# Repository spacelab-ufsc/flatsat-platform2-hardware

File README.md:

<h1 align="center">
	FLATSAT PLATFORM V2.0 - HARDWARE
	<br>
</h1>

<h4 align="center">Hardware project of the FlatSat Platform 2.0, designed and developed by SpaceLab.</h4>

<p align="center">

</p>

<details>
    <summary>Summary</summary>
    <ol>
        <li>
            <a href="#overview">Overview</a>
        </li>
        <li>
            <a href="#repository-organization">Repository Organization</a>
        </li>
        <li>
            <a href="#license">License</a>
        </li>
        <li>
            <a href="#releases">Releases</a>
        </li>
        <li>
            <a href="#notes">Notes</a>
        </li>
        <li>
            <a href="#references">References</a>
        </li>
    </ol>
</details>

## Overview
The **FlatSat Platform 2.0** is a testbench for testing the main SpaceLab's subsystems, but can be adapted for other CubeSat missions. A FlatSat is an electrical model of the satellite with the subsystems assembled side by side over a workbench that can be mounted during the V&V [[1]](#1). They offer an easier, faster and safer way for testing subsystems before assembly into the final structure of a CubeSat. It can be used in combination with the hardware-in-the-loop (HIL) technique, which justifies the usage of a built-in MicroZed and sensors. Moreover, it supports up to 6 modules. This platform is intended to function as an electrical ground support equipment (EGSE) for the SpaceLab team, leveraging the MicroZed, sensors, and future daughterboards to emulate and simulate diverse mission scenarios. Additionally, it facilitates comprehensive system-level and subsystem-level testing. The FlatSat Platform itself is presented in [[2]](#2).

This repository contains the hardware project of the FlatSat Platform 2.0 (schematics, PCB layout, libraries and fabrication files), developed in KiCad.

<p align="center">

</p>

## Repository Organization
`sources`: KiCad project (schematics, PCB layout, project settings and library tables).

`lib`: Project libraries: symbols (`*.kicad_sym`), footprints (`lib.pretty`), 3D models (`lib.3dshapes`) and the symbol generator (`lib.gen`).

`altium_import`: Symbols, footprints and 3D models converted from the original Altium project.

`fab`: Fabrication files (Gerbers, drill and placement files) and the script that packages them.

`outputs`: Project outputs, such as schematic PDF and board renders.

`kibot.yml`: [KiBot](https://github.com/INTI-CMNB/KiBot) configuration for generating the outputs.

## License
This repository is open-source under the CERN Open Hardware Licence Version 2 - Strongly Reciprocal (CERN-OHL-S-2.0).

## Releases
The FlatSat Platform hardware, firmware and documentation releases are synchronized in order to guarantee compatibility. Using different versions might lead to unpredictable behavior. Refer to the [documentation](https://github.com/spacelab-ufsc/flatsat-platform2) for compatibility notes.

## Notes
Related repositories: [FlatSat Platform 2.0](https://github.com/spacelab-ufsc/flatsat-platform2) (main repository and documentation) and [FlatSat Platform 2.0 Firmware](https://github.com/spacelab-ufsc/flatsat-platform2-firmware).

For more info about the SpaceLab, access our [GitHub](https://github.com/spacelab-ufsc/spacelab), [Linkedin](https://br.linkedin.com/company/spacelab-ufsc) or our [website](https://spacelab.ufsc.br/en/home/).

## References
<a id="1">[1]</a> J. C. E. Barcellos, A. W. Spengler, L. O. Seman, R. D. C. e. Silva, H. P. Roldán and E. A. Bezerra, "FlatSat Platforms for Small Satellites: A Systematic Mapping and Classification," in IEEE Journal on Miniaturization for Air and Space Systems, vol. 4, no. 2, pp. 186-198, June 2023, doi: 10.1109/JMASS.2023.3249044. Available [here](https://ieeexplore.ieee.org/document/10052660).

<a id="2">[2]</a> J. C. E. Barcellos, C. A. P. Freitas, V. N. Kürschner, V. G. P. Curtarelli, E. A. Bezerra; A. W. Spengler, "An Open-Source, Reconfigurable FlatSat Platform for CubeSat Verification: Design and Validation," in IEEE Journal on Miniaturization for Air and Space Systems, vol. 7, no. 3, pp. 334 - 347, September 2026, doi:10.1109/JMASS.2026.3706017. Available [here](https://ieeexplore.ieee.org/document/11574658).

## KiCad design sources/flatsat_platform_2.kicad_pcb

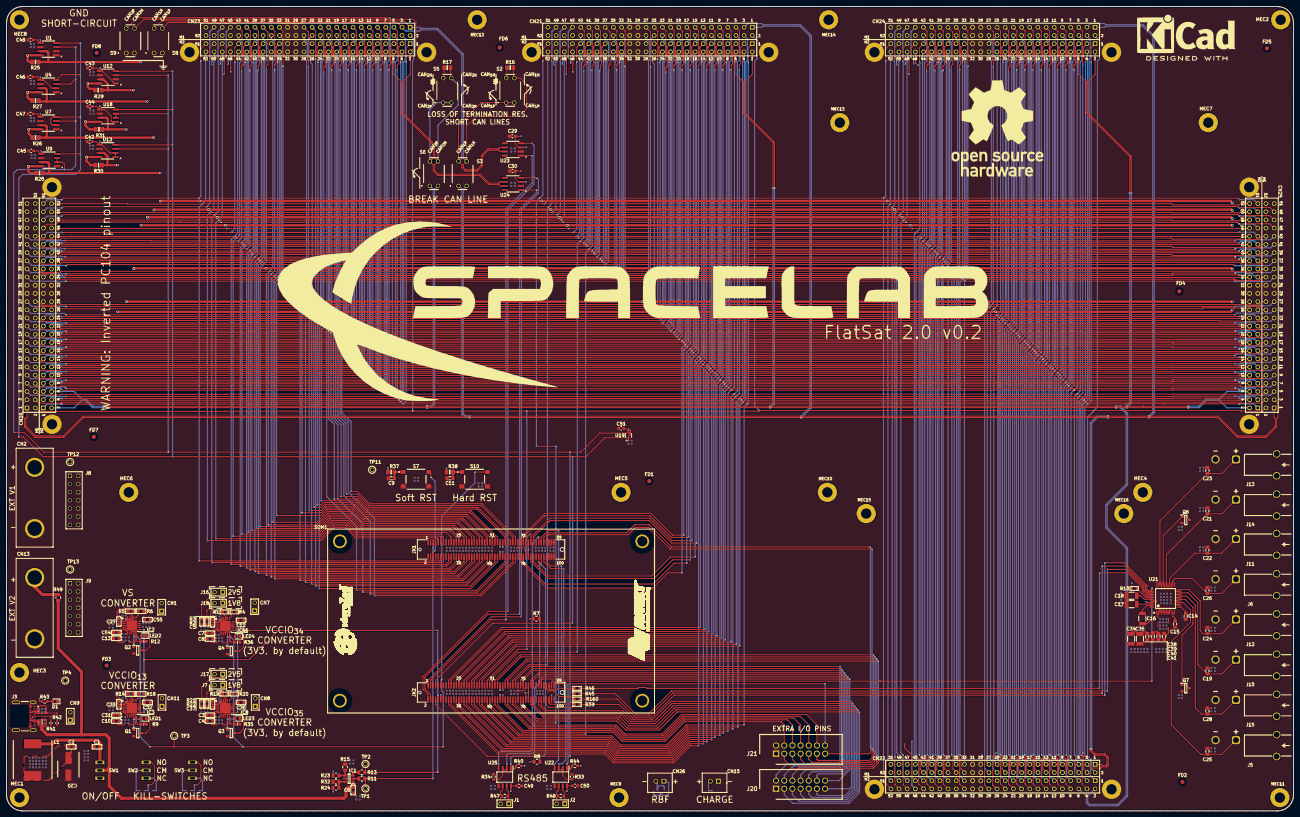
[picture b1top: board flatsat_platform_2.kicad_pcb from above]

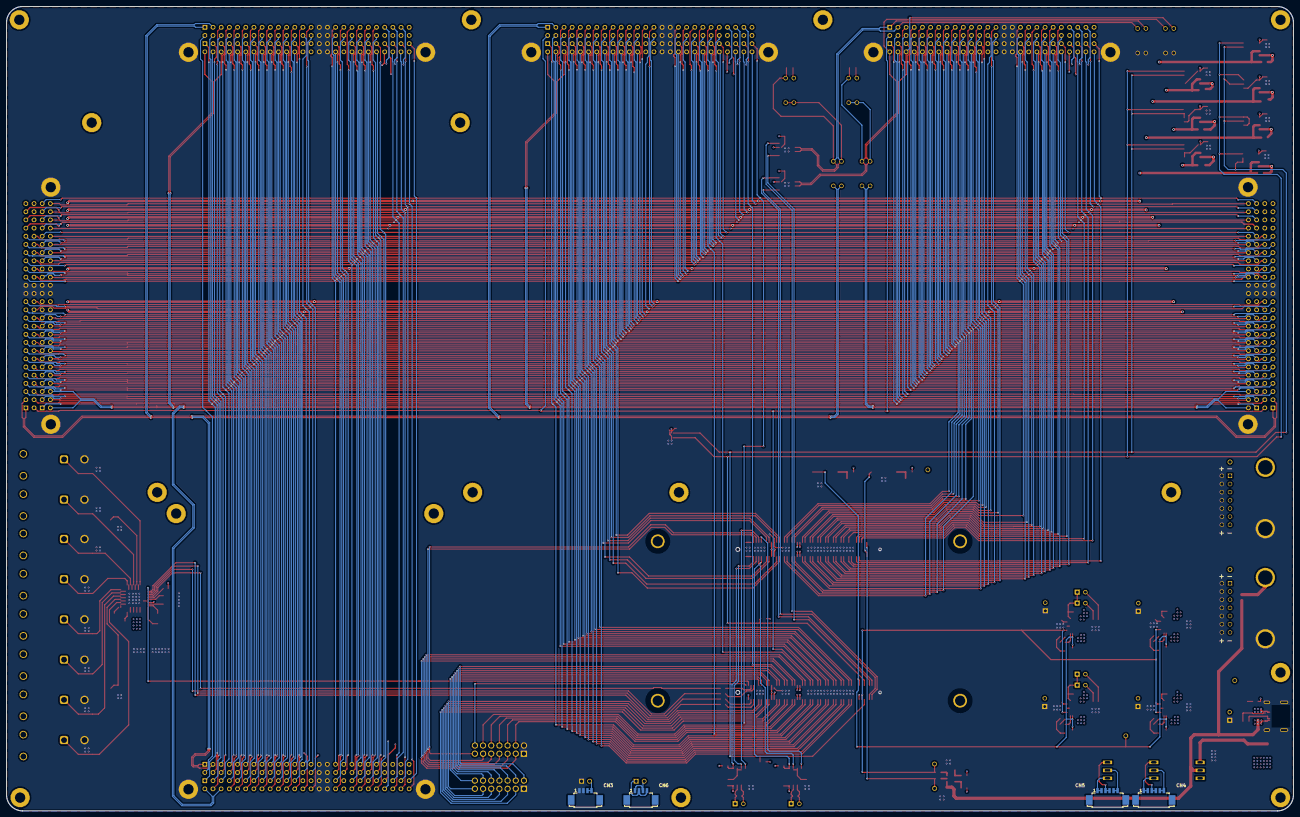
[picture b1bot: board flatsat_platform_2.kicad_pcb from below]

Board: 4 copper layers, 400.0 x 250.0 mm, 214 parts (4 on the bottom side), 221 nets.

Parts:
C1: GRM188R71C103KA01D; C0603_MD
C2: CL10B104KA8NNNC; C0603_MD
C3, C4, C7, C8, C10, C13, C31, C54: UMK107BJ105KA-T; C0603_MD
C5, C27, C33, C37: GRM188C81C106MA73D; C0603_MD
C6: GRM188R71H104JA93D; C0603_MD
C9, C11, C19, C21, C22, C23, C24, C25, C26, C28, C38, C39, C40, C41: 0.1uF/25V; CC0805
C12, C32, C36, C55: CL10B103KB8NNNC; C0603_MD
C14, C15: 1.0uF/50V; CC0805
C16, C17, C18, C34, C35: 10uF/16V; CC1210
C20: 865080845004; CAPAE660X770N
C29, C30: 100nF/50V; CC0603
C42, C43, C44, C45, C46, C47, C48, C49, C50, C51: 100nF; CAP0603
CN1, CN7, CN8, CN9, CN11: 5-146285-2; PIN BAR 2 2.54mm 180 GRAUS
CN2, CN13: 4243-0
CN3, CN6: 4 pin Picoblade; PICO BLADE 0532610471
CN4, CN5: 6 pin Picoblade; PICO BLADE 0532610671
CN15, CN26: JST 2 position header 2.5mm; B2B-XH-A-M(LF)(SN)
CN20: PC104_inverted; PC104_INVERTED
CN21, CN22, CN23, CN24, CN25: PC104
D1: LED; LED_0603_1608Metric
FD1, FD2, FD3, FD4, FD5, FD6, FD7, FD8: Fiducial 1.3; Fiducial 1.3mm
IC1: TPS3780BDBVT
IC2, IC3, IC8, IC66: TPS74401RGWRM3; QFN65P500X500X100-21N-D
J1, J2, J7, J16, J17, J18: 5-146280-2; PIN BAR 2 2.54mm 180 GRAUS
J3: 1054500101; FP-1054500101-MFG
J5, J6, J10, J11, J12, J13, J14, J15: PCC-SMP-V-K-5
J8, J9: 87832-1420; SAMTEC_TSW-107-05-F-D
J20, J21: 61201421621
L1: 742792901; WE-PF_7427929...60
LED1, LED2, LED3, LED4: LTST-C190GKT
MEC1, MEC2, MEC3, MEC4, MEC5, MEC6, MEC7, MEC8, MEC9, MEC10, MEC11, MEC12, MEC13, MEC14, MEC15, MEC16: M3; M3 HOLE
Q1, Q2, Q3, Q4: BSS138
Q6, Q7: MMBT3904; SOT95P240X120-3N
R1, R19: RMCF0603FT47K0; R0603_HD
R2, R22: ERJ-PB3B2492V; R0603_HD
R3, R21: ERJ-H3ED5362V; R0603_HD
R4, R20: ERJ-H3ED3752V; R0603_HD
R5, R14: RMCF0603FT3K57; R0603_MD
R6, R18: CPF0603F1K15C1; R0603_MD
R7, R8: 2.2k; RES0805
R9, R12, R35, R36: CRCW06031K00FKEAHP
R10: ERJH3ED3652V; R0603_HD
R11, R13, R49: 0R; RES0805
R15, R23: 100k; RES0805
R16, R17: 120R; 0805
R24: 226k; RES0805
R25, R26, R27, R28, R29, R30, R31: 47m; 0805
R32: 280k; RES0805
R33, R34, R40, R44: 10k; RES0603
R37, R38: DNP; 0805
R39, R45, R46, R160: CRCW060350R0FKEA; R0603_HD
R41, R42: 5.11k; RES0402
R43: 1k; RES0603
R47, R48: 120R; RES0603
S2, S3, S5, S6, S8, S9: NDS02V
S7, S10: 430182043816
SOM1: MicroZed; MICROZEDSOM
SW1, SW2, SW3: SW-T3-2B-A-A3-S1
TP1, TP2, TP3, TP4, TP11, TP12, TP13: TEST POINT PTH
U1, U4, U7, U9, U12, U13, U18: INA219AID; SOIC127P599X175-8N
U19: TMP112AIDRLT; SOT50P160X60-6N
U21: LTC2983CLX#PBF; QFP50P900X900X160-48N
U22, U25: THVD1450DR
U23, U24: SN65HVD232D

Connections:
+5V: C2.1, C3.1, C4.1, C7.1, C8.1, C10.1, C13.1, C20.1 (+), C31.1, C54.1, CN9.2, IC2.5 (IN_1), IC2.6 (IN_2), IC2.7 (IN_3), IC2.8 (IN_4), IC2.10 (BIAS), IC3.5 (IN_1), IC3.6 (IN_2), IC3.7 (IN_3), IC3.8 (IN_4), IC3.10 (BIAS), IC8.5 (IN_1), IC8.6 (IN_2), IC8.7 (IN_3), IC8.8 (IN_4), IC8.10 (BIAS), IC66.5 (IN_1), IC66.6 (IN_2), IC66.7 (IN_3), IC66.8 (IN_4), IC66.10 (BIAS), L1.2, R9.1, R12.1, R24.2, R32.2, R35.1, R36.1, R43.2, SOM1.JX1-57 (VIN_HDR), SOM1.JX1-58 (VIN_HDR), SOM1.JX1-59 (VIN_HDR), SOM1.JX1-60 (VIN_HDR), SOM1.JX2-12 (VIN_HDR), SOM1.JX2-57 (VIN_HDR), SOM1.JX2-58 (VIN_HDR), SOM1.JX2-59 (VIN_HDR), SOM1.JX2-60 (VIN_HDR), TP4.1
/CAN_CHN_1_N: CN23.1 (H1-1), R16.1, S2.3 (NO_1), S3.3 (NO_1), S8.4 (NO_2), U23.6 (CANL)
/CAN_CHN_1_P: CN23.3 (H1-3), S2.1 (COM_1), S2.2 (COM_2), S3.4 (NO_2), S8.3 (NO_1), U23.7 (CANH)
/CAN_CHN_2_N: CN23.54 (H2-2), R17.1, S5.3 (NO_1), S6.3 (NO_1), S9.3 (NO_1), U24.6 (CANL)
/CAN_CHN_2_P: CN23.58 (H2-6), S5.1 (COM_1), S5.2 (COM_2), S6.4 (NO_2), S9.4 (NO_2), U24.7 (CANH)
/CLK_CHN_1: CN20.35 (H1-35), CN21.35 (H1-35), CN22.35 (H1-35), CN23.35 (H1-35), CN24.35 (H1-35), CN25.35 (H1-35), SOM1.JX1-35 (JX1_LVDS_8_P)
/CLK_CHN_2: CN20.64 (H2-12), CN21.64 (H2-12), CN22.64 (H2-12), CN23.64 (H2-12), CN24.64 (H2-12), CN25.64 (H2-12), SOM1.JX2-19 (JX2_LVDS_0_N)
/CLK_CHN_3: R39.1, U21.38 (SCK)
/CS_CHN_1: CN20.40 (H1-40), CN21.40 (H1-40), CN22.40 (H1-40), CN23.40 (H1-40), CN24.40 (H1-40), CN25.40 (H1-40), SOM1.JX1-26 (JX1_LVDS_5_N)
/CS_CHN_2: CN20.65 (H2-13), CN21.65 (H2-13), CN22.65 (H2-13), CN23.65 (H2-13), CN24.65 (H2-13), CN25.65 (H2-13), SOM1.JX1-84 (JX1_LVDS_23_N)
/CS_CHN_3: R46.2, U21.41 (~CS)
/EPS_H1-46: CN20.45 (H1-45), CN20.46 (H1-46), R25.1, U1.8 (VIN+)
/EPS_H1-48: CN20.47 (H1-47), CN20.48 (H1-48), R27.1, U4.8 (VIN+)
/EPS_H1-50: CN20.49 (H1-49), CN20.50 (H1-50), R26.1, U7.8 (VIN+)
/EPS_H1-52: CN20.51 (H1-51), CN20.52 (H1-52), R28.1, U9.8 (VIN+)
/EPS_H2-26: CN20.77 (H2-25), CN20.78 (H2-26), R30.1, U13.8 (VIN+)
/EPS_H2-28: CN20.79 (H2-27), CN20.80 (H2-28), R31.1, U18.8 (VIN+)
/EPS_H2-36: CN20.87 (H2-35), CN20.88 (H2-36), R29.1, U12.8 (VIN+)
/H1-46: CN21.45 (H1-45), CN21.46 (H1-46), CN22.45 (H1-45), CN22.46 (H1-46), CN23.45 (H1-45), CN23.46 (H1-46), CN24.45 (H1-45), CN24.46 (H1-46), CN25.45 (H1-45), CN25.46 (H1-46), R25.2, U1.7 (VIN-)
/H1-48: CN21.47 (H1-47), CN21.48 (H1-48), CN22.47 (H1-47), CN22.48 (H1-48), CN23.47 (H1-47), CN23.48 (H1-48), CN24.47 (H1-47), CN24.48 (H1-48), CN25.47 (H1-47), CN25.48 (H1-48), R27.2, U4.7 (VIN-)
/H1-50: CN21.49 (H1-49), CN21.50 (H1-50), CN22.49 (H1-49), CN22.50 (H1-50), CN23.49 (H1-49), CN23.50 (H1-50), CN24.49 (H1-49), CN24.50 (H1-50), CN25.49 (H1-49), CN25.50 (H1-50), R26.2, U7.7 (VIN-)
/H1-52: CN21.51 (H1-51), CN21.52 (H1-52), CN22.51 (H1-51), CN22.52 (H1-52), CN23.51 (H1-51), CN23.52 (H1-52), CN24.51 (H1-51), CN24.52 (H1-52), CN25.51 (H1-51), CN25.52 (H1-52), R28.2, U9.7 (VIN-)
/H1_N: CN20.1 (H1-1), CN21.1 (H1-1), CN22.1 (H1-1), CN24.1 (H1-1), CN25.1 (H1-1), S3.2 (COM_2)
/H1_P: CN20.3 (H1-3), CN21.3 (H1-3), CN22.3 (H1-3), CN24.3 (H1-3), CN25.3 (H1-3), S3.1 (COM_1)
/H2-26: CN21.77 (H2-25), CN21.78 (H2-26), CN22.77 (H2-25), CN22.78 (H2-26), CN23.77 (H2-25), CN23.78 (H2-26), CN24.77 (H2-25), CN24.78 (H2-26), CN25.77 (H2-25), CN25.78 (H2-26), R30.2, U13.7 (VIN-)
/H2-28: CN21.79 (H2-27), CN21.80 (H2-28), CN22.79 (H2-27), CN22.80 (H2-28), CN23.79 (H2-27), CN23.80 (H2-28), CN24.79 (H2-27), CN24.80 (H2-28), CN25.79 (H2-27), CN25.80 (H2-28), R31.2, U18.7 (VIN-)
/H2-36: CN21.87 (H2-35), CN21.88 (H2-36), CN22.87 (H2-35), CN22.88 (H2-36), CN23.87 (H2-35), CN23.88 (H2-36), CN24.87 (H2-35), CN24.88 (H2-36), CN25.87 (H2-35), CN25.88 (H2-36), R29.2, U12.7 (VIN-)
/H2_N: CN20.54 (H2-2), CN21.54 (H2-2), CN22.54 (H2-2), CN24.54 (H2-2), CN25.54 (H2-2), S6.2 (COM_2)
/H2_P: CN20.58 (H2-6), CN21.58 (H2-6), CN22.58 (H2-6), CN24.58 (H2-6), CN25.58 (H2-6), S6.1 (COM_1)
/LTC_ITR: SOM1.JX2-97 (BANK13_LVDS_6_P), U21.37 (INTERRUPT)
/MISO_CHN_1: CN20.37 (H1-37), CN21.37 (H1-37), CN22.37 (H1-37), CN23.37 (H1-37), CN24.37 (H1-37), CN25.37 (H1-37), SOM1.JX1-31 (JX1_LVDS_6_N)
/MISO_CHN_2: CN20.66 (H2-14), CN21.66 (H2-14), CN22.66 (H2-14), CN23.66 (H2-14), CN24.66 (H2-14), CN25.66 (H2-14), SOM1.JX1-83 (JX1_LVDS_22_N)
/MISO_CHN_3: R160.1, U21.39 (SDO)
/MOSI_CHN_1: CN20.39 (H1-39), CN21.39 (H1-39), CN22.39 (H1-39), CN23.39 (H1-39), CN24.39 (H1-39), CN25.39 (H1-39), SOM1.JX1-25 (JX1_LVDS_4_N)
/MOSI_CHN_2: CN20.63 (H2-11), CN21.63 (H2-11), CN22.63 (H2-11), CN23.63 (H2-11), CN24.63 (H2-11), CN25.63 (H2-11), SOM1.JX2-20 (JX2_LVDS_1_N)
/MOSI_CHN_3: R45.2, U21.40 (SDI)
/P1: CN20.104 (H2-52), CN21.104 (H2-52), CN22.104 (H2-52), CN23.104 (H2-52), CN24.104 (H2-52), CN25.104 (H2-52), SOM1.JX1-12 (JX1_LVDS_1_P)
/P2: CN20.102 (H2-50), CN21.102 (H2-50), CN22.102 (H2-50), CN23.102 (H2-50), CN24.102 (H2-50), CN25.102 (H2-50), SOM1.JX1-9 (JX1_SE_0)
/P3: CN20.99 (H2-47), CN21.99 (H2-47), CN22.99 (H2-47), CN23.99 (H2-47), CN24.99 (H2-47), CN25.99 (H2-47), SOM1.JX1-14 (JX1_LVDS_1_N)
/P4: CN20.100 (H2-48), CN21.100 (H2-48), CN22.100 (H2-48), CN23.100 (H2-48), CN24.100 (H2-48), CN25.100 (H2-48), SOM1.JX1-11 (JX1_LVDS_0_P)
/P5: CN20.96 (H2-44), CN21.96 (H2-44), CN22.96 (H2-44), CN23.96 (H2-44), CN24.96 (H2-44), CN25.96 (H2-44), SOM1.JX1-18 (JX1_LVDS_3_P)
/P6: CN20.44 (H1-44), CN21.44 (H1-44), CN22.44 (H1-44), CN23.44 (H1-44), CN24.44 (H1-44), CN25.44 (H1-44), SOM1.JX1-13 (JX1_LVDS_0_N)
/P7: CN20.94 (H2-42), CN21.94 (H2-42), CN22.94 (H2-42), CN23.94 (H2-42), CN24.94 (H2-42), CN25.94 (H2-42), SOM1.JX1-20 (JX1_LVDS_3_N)
/P8: CN20.42 (H1-42), CN21.42 (H1-42), CN22.42 (H1-42), CN23.42 (H1-42), CN24.42 (H1-42), CN25.42 (H1-42), SOM1.JX1-19 (JX1_LVDS_2_N)
/P9: CN20.91 (H2-39), CN21.91 (H2-39), CN22.91 (H2-39), CN23.91 (H2-39), CN24.91 (H2-39), CN25.91 (H2-39), SOM1.JX1-24 (JX1_LVDS_5_P)
/P10: CN20.92 (H2-40), CN21.92 (H2-40), CN22.92 (H2-40), CN23.92 (H2-40), CN24.92 (H2-40), CN25.92 (H2-40), SOM1.JX1-23 (JX1_LVDS_4_P)
/P11: CN20.89 (H2-37), CN21.89 (H2-37), CN22.89 (H2-37), CN23.89 (H2-37), CN24.89 (H2-37), CN25.89 (H2-37), SOM1.JX1-30 (JX1_LVDS_7_P)
/P12: CN20.90 (H2-38), CN21.90 (H2-38), CN22.90 (H2-38), CN23.90 (H2-38), CN24.90 (H2-38), CN25.90 (H2-38), SOM1.JX1-29 (JX1_LVDS_6_P)
/P13: CN20.38 (H1-38), CN21.38 (H1-38), CN22.38 (H1-38), CN23.38 (H1-38), CN24.38 (H1-38), CN25.38 (H1-38), SOM1.JX1-32 (JX1_LVDS_7_N)
/P14: CN20.36 (H1-36), CN21.36 (H1-36), CN22.36 (H1-36), CN23.36 (H1-36), CN24.36 (H1-36), CN25.36 (H1-36), SOM1.JX1-36 (JX1_LVDS_9_P)
/P15: CN20.85 (H2-33), CN21.85 (H2-33), CN22.85 (H2-33), CN23.85 (H2-33), CN24.85 (H2-33), CN25.85 (H2-33), SOM1.JX1-38 (JX1_LVDS_9_N)
/P16: CN20.86 (H2-34), CN21.86 (H2-34), CN22.86 (H2-34), CN23.86 (H2-34), CN24.86 (H2-34), CN25.86 (H2-34), SOM1.JX1-37 (JX1_LVDS_8_N)
/P17: CN20.34 (H1-34), CN21.34 (H1-34), CN22.34 (H1-34), CN23.34 (H1-34), CN24.34 (H1-34), CN25.34 (H1-34), SOM1.JX1-42 (JX1_LVDS_11_P)
/P18: CN20.33 (H1-33), CN21.33 (H1-33), CN22.33 (H1-33), CN23.33 (H1-33), CN24.33 (H1-33), CN25.33 (H1-33), SOM1.JX1-41 (JX1_LVDS_10_P)
/P19: CN20.28 (H1-28), CN21.28 (H1-28), CN22.28 (H1-28), CN23.28 (H1-28), CN24.28 (H1-28), CN25.28 (H1-28), SOM1.JX1-44 (JX1_LVDS_11_N)
/P20: CN20.27 (H1-27), CN21.27 (H1-27), CN22.27 (H1-27), CN23.27 (H1-27), CN24.27 (H1-27), CN25.27 (H1-27), SOM1.JX1-43 (JX1_LVDS_10_N)
/P21: CN20.26 (H1-26), CN21.26 (H1-26), CN22.26 (H1-26), CN23.26 (H1-26), CN24.26 (H1-26), CN25.26 (H1-26), SOM1.JX1-48 (JX1_LVDS_13_P)
/P22: CN20.25 (H1-25), CN21.25 (H1-25), CN22.25 (H1-25), CN23.25 (H1-25), CN24.25 (H1-25), CN25.25 (H1-25), SOM1.JX1-47 (JX1_LVDS_12_P)
/P23: CN20.75 (H2-23), CN21.75 (H2-23), CN22.75 (H2-23), CN23.75 (H2-23), CN24.75 (H2-23), CN25.75 (H2-23), SOM1.JX1-50 (JX1_LVDS_13_N)
/P24: CN20.76 (H2-24), CN21.76 (H2-24), CN22.76 (H2-24), CN23.76 (H2-24), CN24.76 (H2-24), CN25.76 (H2-24), SOM1.JX1-49 (JX1_LVDS_12_N)
/P25: CN20.24 (H1-24), CN21.24 (H1-24), CN22.24 (H1-24), CN23.24 (H1-24), CN24.24 (H1-24), CN25.24 (H1-24), SOM1.JX1-54 (JX1_LVDS_15_P)
/P26: CN20.23 (H1-23), CN21.23 (H1-23), CN22.23 (H1-23), CN23.23 (H1-23), CN24.23 (H1-23), CN25.23 (H1-23), SOM1.JX1-53 (JX1_LVDS_14_P)
/P27: CN20.73 (H2-21), CN21.73 (H2-21), CN22.73 (H2-21), CN23.73 (H2-21), CN24.73 (H2-21), CN25.73 (H2-21), SOM1.JX1-56 (JX1_LVDS_15_N)
/P28: CN20.74 (H2-22), CN21.74 (H2-22), CN22.74 (H2-22), CN23.74 (H2-22), CN24.74 (H2-22), CN25.74 (H2-22), SOM1.JX1-55 (JX1_LVDS_14_N)
/P29: CN20.22 (H1-22), CN21.22 (H1-22), CN22.22 (H1-22), CN23.22 (H1-22), CN24.22 (H1-22), CN25.22 (H1-22), SOM1.JX1-62 (JX1_LVDS_17_P)
/P30: CN20.21 (H1-21), CN21.21 (H1-21), CN22.21 (H1-21), CN23.21 (H1-21), CN24.21 (H1-21), CN25.21 (H1-21), SOM1.JX1-61 (JX1_LVDS_16_P)
/P31: CN20.71 (H2-19), CN21.71 (H2-19), CN22.71 (H2-19), CN23.71 (H2-19), CN24.71 (H2-19), CN25.71 (H2-19), SOM1.JX1-64 (JX1_LVDS_17_N)
/P32: CN20.72 (H2-20), CN21.72 (H2-20), CN22.72 (H2-20), CN23.72 (H2-20), CN24.72 (H2-20), CN25.72 (H2-20), SOM1.JX1-63 (JX1_LVDS_16_N)
/P33: CN20.20 (H1-20), CN21.20 (H1-20), CN22.20 (H1-20), CN23.20 (H1-20), CN24.20 (H1-20), CN25.20 (H1-20), SOM1.JX1-68 (JX1_LVDS_19_P)
/P34: CN20.69 (H2-17), CN21.69 (H2-17), CN22.69 (H2-17), CN23.69 (H2-17), CN24.69 (H2-17), CN25.69 (H2-17), SOM1.JX1-70 (JX1_LVDS_19_N)
/P35: CN20.70 (H2-18), CN21.70 (H2-18), CN22.70 (H2-18), CN23.70 (H2-18), CN24.70 (H2-18), CN25.70 (H2-18), SOM1.JX1-69 (JX1_LVDS_18_N)
/P36: CN20.18 (H1-18), CN21.18 (H1-18), CN22.18 (H1-18), CN23.18 (H1-18), CN24.18 (H1-18), CN25.18 (H1-18), SOM1.JX1-74 (JX1_LVDS_21_P)
/P37: CN20.67 (H2-15), CN21.67 (H2-15), CN22.67 (H2-15), CN23.67 (H2-15), CN24.67 (H2-15), CN25.67 (H2-15), SOM1.JX1-76 (JX1_LVDS_21_N)
/P38: CN20.68 (H2-16), CN21.68 (H2-16), CN22.68 (H2-16), CN23.68 (H2-16), CN24.68 (H2-16), CN25.68 (H2-16), SOM1.JX1-75 (JX1_LVDS_20_N)
/P39: CN20.16 (H1-16), CN21.16 (H1-16), CN22.16 (H1-16), CN23.16 (H1-16), CN24.16 (H1-16), CN25.16 (H1-16), SOM1.JX1-82 (JX1_LVDS_23_P)
/P40: CN20.15 (H1-15), CN21.15 (H1-15), CN22.15 (H1-15), CN23.15 (H1-15), CN24.15 (H1-15), CN25.15 (H1-15), SOM1.JX1-81 (JX1_LVDS_22_P)
/P41: CN20.14 (H1-14), CN21.14 (H1-14), CN22.14 (H1-14), CN23.14 (H1-14), CN24.14 (H1-14), CN25.14 (H1-14), SOM1.JX2-18 (JX2_LVDS_1_P)
/P42: CN20.13 (H1-13), CN21.13 (H1-13), CN22.13 (H1-13), CN23.13 (H1-13), CN24.13 (H1-13), CN25.13 (H1-13), SOM1.JX2-17 (JX2_LVDS_0_P)
/P43: CN20.12 (H1-12), CN21.12 (H1-12), CN22.12 (H1-12), CN23.12 (H1-12), CN24.12 (H1-12), CN25.12 (H1-12), SOM1.JX2-24 (JX2_LVDS_3_P)
/P44: CN20.11 (H1-11), CN21.11 (H1-11), CN22.11 (H1-11), CN23.11 (H1-11), CN24.11 (H1-11), CN25.11 (H1-11), SOM1.JX2-23 (JX2_LVDS_2_P)
/P45: CN20.61 (H2-9), CN21.61 (H2-9), CN22.61 (H2-9), CN23.61 (H2-9), CN24.61 (H2-9), CN25.61 (H2-9), SOM1.JX2-26 (JX2_LVDS_3_N)
/P46: CN20.62 (H2-10), CN21.62 (H2-10), CN22.62 (H2-10), CN23.62 (H2-10), CN24.62 (H2-10), CN25.62 (H2-10), SOM1.JX2-25 (JX2_LVDS_2_N)
/P47: CN20.10 (H1-10), CN21.10 (H1-10), CN22.10 (H1-10), CN23.10 (H1-10), CN24.10 (H1-10), CN25.10 (H1-10), SOM1.JX2-30 (JX2_LVDS_5_P)
/P48: CN20.9 (H1-9), CN21.9 (H1-9), CN22.9 (H1-9), CN23.9 (H1-9), CN24.9 (H1-9), CN25.9 (H1-9), SOM1.JX2-29 (JX2_LVDS_4_P)
/P49: CN20.60 (H2-8), CN21.60 (H2-8), CN22.60 (H2-8), CN23.60 (H2-8), CN24.60 (H2-8), CN25.60 (H2-8), SOM1.JX2-31 (JX2_LVDS_4_N)
/P50: CN20.8 (H1-8), CN21.8 (H1-8), CN22.8 (H1-8), CN23.8 (H1-8), CN24.8 (H1-8), CN25.8 (H1-8), SOM1.JX2-36 (JX2_LVDS_7_P)
/P51: CN20.7 (H1-7), CN21.7 (H1-7), CN22.7 (H1-7), CN23.7 (H1-7), CN24.7 (H1-7), CN25.7 (H1-7), SOM1.JX2-35 (JX2_LVDS_6_P)
/P52: CN20.6 (H1-6), CN21.6 (H1-6), CN22.6 (H1-6), CN23.6 (H1-6), CN24.6 (H1-6), CN25.6 (H1-6), SOM1.JX2-37 (JX2_LVDS_6_N)
/P53: CN20.5 (H1-5), CN21.5 (H1-5), CN22.5 (H1-5), CN23.5 (H1-5), CN24.5 (H1-5), CN25.5 (H1-5), SOM1.JX2-42 (JX2_LVDS_9_P)
/P54: CN20.55 (H2-3), CN21.55 (H2-3), CN22.55 (H2-3), CN23.55 (H2-3), CN24.55 (H2-3), CN25.55 (H2-3), SOM1.JX2-41 (JX2_LVDS_8_P)
/P55: CN20.56 (H2-4), CN21.56 (H2-4), CN22.56 (H2-4), CN23.56 (H2-4), CN24.56 (H2-4), CN25.56 (H2-4), SOM1.JX2-44 (JX2_LVDS_9_N)
/P56: CN20.4 (H1-4), CN21.4 (H1-4), CN22.4 (H1-4), CN23.4 (H1-4), CN24.4 (H1-4), CN25.4 (H1-4), SOM1.JX2-43 (JX2_LVDS_8_N)
/P57: CN20.53 (H2-1), CN21.53 (H2-1), CN22.53 (H2-1), CN23.53 (H2-1), CN24.53 (H2-1), CN25.53 (H2-1), SOM1.JX2-48 (JX2_LVDS_11_P)
/P58: CN20.2 (H1-2), CN21.2 (H1-2), CN22.2 (H1-2), CN23.2 (H1-2), CN24.2 (H1-2), CN25.2 (H1-2), SOM1.JX2-47 (JX2_LVDS_10_P)
/PC104/H2-41: CN20.93 (H2-41), CN21.93 (H2-41), CN22.93 (H2-41), CN23.93 (H2-41), CN24.93 (H2-41), CN25.93 (H2-41)
/PC104/H2-43: CN20.95 (H2-43), CN21.95 (H2-43), CN22.95 (H2-43), CN23.95 (H2-43), CN24.95 (H2-43), CN25.95 (H2-43)
/PC104/H2-45: CN20.97 (H2-45), CN21.97 (H2-45), CN22.97 (H2-45), CN23.97 (H2-45), CN24.97 (H2-45), CN25.97 (H2-45)
/PC104/H2-46: CN20.98 (H2-46), CN21.98 (H2-46), CN22.98 (H2-46), CN23.98 (H2-46), CN24.98 (H2-46), CN25.98 (H2-46)
/PG_CARRIER: IC2.9 (PG), IC3.9 (PG), IC8.9 (PG), IC66.9 (PG), Q1.1 (G), Q2.1 (G), Q3.1 (G), Q4.1 (G), S10.3 (COM_2), SOM1.JX2-11 (PG_CARRIER), TP3.1
/PWR_EN: R11.2, SOM1.JX1-5 (PWR_ENABLE), TP1.1
/RXD_CHN_1: SOM1.JX2-2 (MIO10), U23.4 (RXD)
/RXD_CHN_2: SOM1.JX2-1 (MIO13), U24.4 (RXD)
/RX_CHN_1: CN20.17 (H1-17), CN21.17 (H1-17), CN22.17 (H1-17), CN23.17 (H1-17), CN24.17 (H1-17), CN25.17 (H1-17), SOM1.JX1-73 (JX1_LVDS_20_P)
/RX_CHN_2: CN20.57 (H2-5), CN21.57 (H2-5), CN22.57 (H2-5), CN23.57 (H2-5), CN24.57 (H2-5), CN25.57 (H2-5), SOM1.JX2-38 (JX2_LVDS_7_N)
/RX_CHN_3: R44.1, SOM1.JX1-92 (BANK13_LVDS_3_P), U22.1 (R)
/RX_CHN_4: R40.1, SOM1.JX1-88 (BANK13_LVDS_1_P), U25.1 (R)
/SCL_CHN_1: CN20.43 (H1-43), CN21.43 (H1-43), CN22.43 (H1-43), CN23.43 (H1-43), CN24.43 (H1-43), CN25.43 (H1-43), SOM1.JX2-49 (JX2_LVDS_10_N)
/SCL_CHN_2: CN20.103 (H2-51), CN21.103 (H2-51), CN22.103 (H2-51), CN23.103 (H2-51), CN24.103 (H2-51), CN25.103 (H2-51), SOM1.JX2-70 (JX2_LVDS_17_N)
/SCL_CHN_3: R7.2, SOM1.JX2-7 (MIO14), U1.4 (SCL), U4.4 (SCL), U7.2 (A0), U7.4 (SCL), U9.4 (SCL), U12.4 (SCL), U13.4 (SCL), U18.4 (SCL), U19.1 (SCL)
/SDA_CHN_1: CN20.41 (H1-41), CN21.41 (H1-41), CN22.41 (H1-41), CN23.41 (H1-41), CN24.41 (H1-41), CN25.41 (H1-41), SOM1.JX2-50 (JX2_LVDS_11_N)
/SDA_CHN_2: CN20.101 (H2-49), CN21.101 (H2-49), CN22.101 (H2-49), CN23.101 (H2-49), CN24.101 (H2-49), CN25.101 (H2-49), SOM1.JX2-67 (JX2_LVDS_16_P)
/SDA_CHN_3: R8.2, SOM1.JX2-8 (MIO15), U1.3 (SDA), U4.3 (SDA), U7.3 (SDA), U9.2 (A0), U9.3 (SDA), U12.3 (SDA), U13.3 (SDA), U18.2 (A0), U18.3 (SDA), U19.6 (SDA)
/TXD_CHN_1: SOM1.JX2-3 (MIO11), U23.1 (TXD)
/TXD_CHN_2: SOM1.JX2-4 (MIO12), U24.1 (TXD)
/TX_CHN_1: CN20.19 (H1-19), CN21.19 (H1-19), CN22.19 (H1-19), CN23.19 (H1-19), CN24.19 (H1-19), CN25.19 (H1-19), SOM1.JX1-67 (JX1_LVDS_18_P)
/TX_CHN_2: CN20.59 (H2-7), CN21.59 (H2-7), CN22.59 (H2-7), CN23.59 (H2-7), CN24.59 (H2-7), CN25.59 (H2-7), SOM1.JX2-32 (JX2_LVDS_5_N)
/TX_CHN_3: SOM1.JX1-89 (BANK13_LVDS_0_N), U22.4 (D)
/TX_CHN_4: SOM1.JX1-87 (BANK13_LVDS_0_P), U25.4 (D)
/T/R_CHN_3: R33.2, SOM1.JX1-94 (BANK13_LVDS_3_N), U22.2 (~RE), U22.3 (DE)
/T/R_CHN_4: R34.1, SOM1.JX1-90 (BANK13_LVDS_1_N), U25.2 (~RE), U25.3 (DE)
/VCCIO_EN: IC2.11 (EN), IC3.11 (EN), IC8.11 (EN), IC66.11 (EN), R13.2, SOM1.JX2-10 (PG_1V8), TP2.1
/VCCIO_{13}: C33.1, CN11.2, IC3.1 (OUT_1), IC3.18 (OUT_2), IC3.19 (OUT_3), IC3.20 (OUT_4), R14.1, SOM1.JX2-98 (VCCO_13)
/VCCIO_{34}: C5.1, CN7.2, IC66.1 (OUT_1), IC66.18 (OUT_2), IC66.19 (OUT_3), IC66.20 (OUT_4), R1.1, SOM1.JX1-78 (VCCO_34), SOM1.JX1-79 (VCCO_34), SOM1.JX1-80 (VCCO_34)
/VCCIO_{35}: C37.1, CN8.2, IC8.1 (OUT_1), IC8.18 (OUT_2), IC8.19 (OUT_3), IC8.20 (OUT_4), R19.1, SOM1.JX2-78 (VCCO_35), SOM1.JX2-79 (VCCO_35), SOM1.JX2-80 (VCCO_35)
/VS: C27.1, C29.1, C30.1, C34.1, C35.1, C38.1, C39.1, C40.1, C41.1, C42.2, C43.2, C44.2, C45.2, C46.2, C47.2, C48.2, C49.2, C50.2, C51.2, CN1.2, IC2.1 (OUT_1), IC2.18 (OUT_2), IC2.19 (OUT_3), IC2.20 (OUT_4), R5.1, R7.1, R8.1, R10.2, R37.2, R38.2, R40.2, R44.2, TP11.1, U1.5 (VS), U4.2 (A0), U4.5 (VS), U7.5 (VS), U9.5 (VS), U12.1 (A1), U12.5 (VS), U13.1 (A1), U13.2 (A0), U13.5 (VS), U18.1 (A1), U18.5 (VS), U19.5 (V+), U21.2 (VDD_1), U21.4 (VDD_2), U21.6 (VDD_3), U21.8 (VDD_4), U21.45 (VDD_5), U22.8 (VCC), U23.3 (VCC), U24.3 (VCC), U25.8 (VCC)
/kill-switches/+RBF: CN6.2, CN6.4, CN26.1
/kill-switches/-RBF: CN6.1, CN6.3, CN26.2
/kill-switches/COMMON_KILL_SWITCH_1: CN4.5, CN4.6, SW2.2 (COM)
/kill-switches/COMMON_KILL_SWITCH_2: CN5.5, CN5.6, SW3.2 (COM)
/kill-switches/NC_KILL_SWITCH_1: CN4.1, CN4.2, SW2.1
/kill-switches/NC_KILL_SWITCH_2: CN5.1, CN5.2, SW3.1
/kill-switches/NO_KILL_SWITCH_1: CN4.3, CN4.4, SW2.3
/kill-switches/NO_KILL_SWITCH_2: CN5.3, CN5.4, SW3.3
/microzed/CARRIER_SRST#: S7.3 (COM_2), SOM1.JX1-6 (CARRIER_SRST#)
/microzed/PL_B13_2N: J21.11, SOM1.JX1-93 (BANK13_LVDS_2_N)
/microzed/PL_B13_2P: J21.13, SOM1.JX1-91 (BANK13_LVDS_2_P)
/microzed/PL_B13_6N: J21.14, SOM1.JX2-99 (BANK13_LVDS_6_N)
/microzed/PL_JX2_12N: J21.7, SOM1.JX2-55 (JX2_LVDS_12_N)
/microzed/PL_JX2_12P: J21.9, SOM1.JX2-53 (JX2_LVDS_12_P)
/microzed/PL_JX2_13N: J21.6, SOM1.JX2-56 (JX2_LVDS_13_N)
/microzed/PL_JX2_13P: J21.4, SOM1.JX2-54 (JX2_LVDS_13_P)
/microzed/PL_JX2_14N: J21.3, SOM1.JX2-63 (JX2_LVDS_14_N)
/microzed/PL_JX2_14P: J21.5, SOM1.JX2-61 (JX2_LVDS_14_P)
/microzed/PL_JX2_15N: J21.10, SOM1.JX2-64 (JX2_LVDS_15_N)
/microzed/PL_JX2_15P: J21.8, SOM1.JX2-62 (JX2_LVDS_15_P)
/microzed/PL_JX2_16N: J20.2, SOM1.JX2-69 (JX2_LVDS_16_N)
/microzed/PL_JX2_17P: J21.12, SOM1.JX2-68 (JX2_LVDS_17_P)
/microzed/PL_JX2_18N: J20.6, SOM1.JX2-75 (JX2_LVDS_18_N)
/microzed/PL_JX2_18P: J20.4, SOM1.JX2-73 (JX2_LVDS_18_P)
/microzed/PL_JX2_19N: J20.5, SOM1.JX2-76 (JX2_LVDS_19_N)
/microzed/PL_JX2_19P: J20.3, SOM1.JX2-74 (JX2_LVDS_19_P)
/microzed/PL_JX2_20N: J20.10, SOM1.JX2-83 (JX2_LVDS_20_N)
/microzed/PL_JX2_20P: J20.8, SOM1.JX2-81 (JX2_LVDS_20_P)
/microzed/PL_JX2_21N: J20.9, SOM1.JX2-84 (JX2_LVDS_21_N)
/microzed/PL_JX2_21P: J20.7, SOM1.JX2-82 (JX2_LVDS_21_P)
/microzed/PL_JX2_22N: J20.14, SOM1.JX2-89 (JX2_LVDS_22_N)
/microzed/PL_JX2_22P: J20.12, SOM1.JX2-87 (JX2_LVDS_22_P)
/microzed/PL_JX2_23N: J20.13, SOM1.JX2-90 (JX2_LVDS_23_N)
/microzed/PL_JX2_23P: J20.11, SOM1.JX2-88 (JX2_LVDS_23_P)
/power/USB_VBUS: C6.1, IC1.1 (VDD), J3.A4 (VBUS), J3.A9 (VBUS), J3.B4 (VBUS), J3.B9 (VBUS), R49.2, SW1.2 (COM)
/power/V1_E: CN2.1, J8.1, J8.3, J8.5, J8.7, J8.9, J8.11, J8.13, TP12.1
/power/V2_E: CN13.1, J9.1, J9.3, J9.5, J9.7, J9.9, J9.11, J9.13, R49.1, TP13.1
/power/non-fixed-bank-34-converter/FB_VCCIO: IC66.16 (FB), J16.1, J18.1, R1.2, R4.1
/power/non-fixed-bank-35-converter/FB_VCCIO: IC8.16 (FB), J7.1, J17.1, R19.2, R20.1
/temp_sensors/CH1: C25.2, J5.2 (positive), U21.16 (CH1)
/temp_sensors/CH3: Q7.1 (B), Q7.3 (C), U21.18 (CH3)
/temp_sensors/CH5: C28.2, J15.2 (positive), U21.20 (CH5)
/temp_sensors/CH7: C19.2, J10.2 (positive), U21.22 (CH7)
/temp_sensors/CH9: C24.2, J12.2 (positive), U21.24 (CH9)
/temp_sensors/CH11: C26.2, J6.2 (positive), U21.26 (CH11)
/temp_sensors/CH13: C22.2, J11.2 (positive), U21.28 (CH13)
/temp_sensors/CH15: C21.2, J14.2 (positive), U21.30 (CH15)
/temp_sensors/CH17: Q6.1 (B), Q6.3 (C), U21.32 (CH17)
/temp_sensors/CH19: C23.2, J13.2 (positive), U21.34 (CH19)
/voltage_sensors/RS485_01_N: J2.1, R48.1, U22.7 (B)
/voltage_sensors/RS485_01_P: J2.2, R48.2, U22.6 (A)
/voltage_sensors/RS485_02_N: J1.1, R47.1, U25.7 (B)
/voltage_sensors/RS485_02_P: J1.2, R47.2, U25.6 (A)
GND: C1.2, C2.2, C3.2, C4.2, C5.2, C6.2, C7.2, C8.2, C9.2, C10.2, C11.2, C12.2, C13.2, C14.2, C15.2, C17.2, C18.2, C19.1, C20.2 (-), C21.1, C22.1, C23.1, C24.1, C25.1, C26.1, C27.2, C28.1, C29.2, C30.2, C31.2, C32.1, C33.2, C34.2, C35.2, C36.2, C37.2, C38.2, C39.2, C40.2, C41.2, C42.1, C43.1, C44.1, C45.1, C46.1, C47.1, C48.1, C49.1, C50.1, C51.1, C54.2, C55.1, CN1.1, CN2.0, CN3.1, CN3.2, CN7.1, CN8.1, CN9.1, CN11.1, CN13.0, CN15.1, CN20.0 (Mouting), CN20.29 (H1-29), CN20.30 (H1-30), CN20.31 (H1-31), CN20.32 (H1-32), CN20.81 (H2-29), CN20.82 (H2-30), CN20.83 (H2-31), CN20.84 (H2-32), CN21.0 (Mouting), CN21.29 (H1-29), CN21.30 (H1-30), CN21.31 (H1-31), CN21.32 (H1-32), CN21.81 (H2-29), CN21.82 (H2-30), CN21.83 (H2-31), CN21.84 (H2-32), CN22.0 (Mouting), CN22.29 (H1-29), CN22.30 (H1-30), CN22.31 (H1-31), CN22.32 (H1-32), CN22.81 (H2-29), CN22.82 (H2-30), CN22.83 (H2-31), CN22.84 (H2-32), CN23.0 (Mouting), CN23.29 (H1-29), CN23.30 (H1-30), CN23.31 (H1-31), CN23.32 (H1-32), CN23.81 (H2-29), CN23.82 (H2-30), CN23.83 (H2-31), CN23.84 (H2-32), CN24.0 (Mouting), CN24.29 (H1-29), CN24.30 (H1-30), CN24.31 (H1-31), CN24.32 (H1-32), CN24.81 (H2-29), CN24.82 (H2-30), CN24.83 (H2-31), CN24.84 (H2-32), CN25.0 (Mouting), CN25.29 (H1-29), CN25.30 (H1-30), CN25.31 (H1-31), CN25.32 (H1-32), CN25.81 (H2-29), CN25.82 (H2-30), CN25.83 (H2-31), CN25.84 (H2-32), D1.1 (K), IC1.5 (GND), IC2.2 (NC_1), IC2.3 (NC_2), IC2.4 (NC_3), IC2.12 (GND_1), IC2.13 (NC_4), IC2.14 (NC_5), IC2.17 (NC_6), IC2.21 (GND_2), IC3.2 (NC_1), IC3.3 (NC_2), IC3.4 (NC_3), IC3.12 (GND_1), IC3.13 (NC_4), IC3.14 (NC_5), IC3.17 (NC_6), IC3.21 (GND_2), IC8.2 (NC_1), IC8.3 (NC_2), IC8.4 (NC_3), IC8.12 (GND_1), IC8.13 (NC_4), IC8.14 (NC_5), IC8.17 (NC_6), IC8.21 (GND_2), IC66.2 (NC_1), IC66.3 (NC_2), IC66.4 (NC_3), IC66.12 (GND_1), IC66.13 (NC_4), IC66.14 (NC_5), IC66.17 (NC_6), IC66.21 (GND_2), J3.A1 (GND), J3.A12 (GND), J3.B1 (GND), J3.B12 (GND), J3.S1 (SHIELD), J5.1 (negative), J6.1 (negative), J8.2, J8.4, J8.6, J8.8, J8.10, J8.12, J8.14, J9.2, J9.4, J9.6, J9.8, J9.10, J9.12, J9.14, J10.1 (negative), J11.1 (negative), J12.1 (negative), J13.1 (negative), J14.1 (negative), J15.1 (negative), J20.1, J21.1, J21.2, Q1.2 (S), Q2.2 (S), Q3.2 (S), Q4.2 (S), Q6.2 (E), Q7.2 (E), R2.2, R3.2, R4.2, R6.2, R15.1, R18.2, R20.2, R21.2, R22.2, R23.1, R33.1, R34.2, R41.1, R42.1, S7.2 (NO_1), S7.4 (NO_2), S8.1 (COM_1), S8.2 (COM_2), S9.1 (COM_1), S9.2 (COM_2), S10.2 (NO_1), S10.4 (NO_2), SOM1.JX1-15 (GND), SOM1.JX1-16 (GND), SOM1.JX1-21 (GND), SOM1.JX1-22 (GND), SOM1.JX1-27 (GND), SOM1.JX1-28 (GND), SOM1.JX1-33 (GND), SOM1.JX1-34 (GND), SOM1.JX1-39 (GND), SOM1.JX1-40 (GND), SOM1.JX1-45 (GND), SOM1.JX1-46 (GND), SOM1.JX1-51 (GND), SOM1.JX1-52 (GND), SOM1.JX1-65 (GND), SOM1.JX1-66 (GND), SOM1.JX1-71 (GND), SOM1.JX1-72 (GND), SOM1.JX1-77 (GND), SOM1.JX1-85 (GND), SOM1.JX1-86 (GND), SOM1.JX1-95 (GND), SOM1.JX1-96 (GND), SOM1.JX1-97 (VP_0_P), SOM1.JX1-98 (DXP_0_P), SOM1.JX1-99 (VN_0_N), SOM1.JX1-100 (DXN_0_N), SOM1.JX2-15 (GND), SOM1.JX2-16 (GND), SOM1.JX2-21 (GND), SOM1.JX2-22 (GND), SOM1.JX2-27 (GND), SOM1.JX2-28 (GND), SOM1.JX2-33 (GND), SOM1.JX2-34 (GND), SOM1.JX2-39 (GND), SOM1.JX2-40 (GND), SOM1.JX2-45 (GND), SOM1.JX2-46 (GND), SOM1.JX2-51 (GND), SOM1.JX2-52 (GND), SOM1.JX2-65 (GND), SOM1.JX2-66 (GND), SOM1.JX2-71 (GND), SOM1.JX2-72 (GND), SOM1.JX2-77 (GND), SOM1.JX2-85 (GND), SOM1.JX2-86 (GND), SOM1.JX2-91 (GND), SOM1.JX2-92 (GND), U1.1 (A1), U1.2 (A0), U1.6 (GND), U4.1 (A1), U4.6 (GND), U7.1 (A1), U7.6 (GND), U9.1 (A1), U9.6 (GND), U12.2 (A0), U12.6 (GND), U13.6 (GND), U18.6 (GND), U19.2 (GND), U19.4 (ADD0), U21.1 (GND_1), U21.3 (GND_2), U21.5 (GND_3), U21.7 (GND_4), U21.9 (GND_5), U21.12 (GND_6), U21.15 (GND_7), U21.17 (CH2), U21.19 (CH4), U21.21 (CH6), U21.23 (CH8), U21.25 (CH10), U21.27 (CH12), U21.29 (CH14), U21.31 (CH16), U21.33 (CH18), U21.35 (CH20), U21.36 (COM), U21.44 (GND_8), U22.5 (GND), U23.2 (GND), U24.2 (GND), U25.5 (GND)
unnamed: C1.1, L1.1, SW1.3
unnamed: CN3.3, CN3.4, CN15.2
unnamed: D1.2 (A), R43.1
unnamed: IC1.2 (OUT1), R11.1
unnamed: IC1.3 (OUT2), R13.1
unnamed: IC1.6 (SENSE1), R23.2, R24.1
unnamed: IC1.4 (SENSE2), R15.2, R32.1
unnamed: IC2.16 (FB), R5.2, R6.1
unnamed: C55.2, IC2.15 (SS)
unnamed: IC3.16 (FB), R14.2, R18.1
unnamed: C32.2, IC3.15 (SS)
unnamed: C36.1, IC8.15 (SS)
unnamed: C12.1, IC66.15 (SS)
unnamed: J3.A5 (CC1), R42.2
unnamed: J3.B5 (CC2), R41.2
unnamed: J7.2, R22.1
unnamed: J16.2, R2.1
unnamed: J17.2, R21.1
unnamed: J18.2, R3.1
unnamed: LED1.2 (A), R9.2
unnamed: LED1.1 (K), Q1.3 (D)
unnamed: LED2.2 (A), R12.2
unnamed: LED2.1 (K), Q2.3 (D)
unnamed: LED3.2 (A), R35.2
unnamed: LED3.1 (K), Q3.3 (D)
unnamed: LED4.2 (A), R36.2
unnamed: LED4.1 (K), Q4.3 (D)
unnamed: R16.2, S2.4 (NO_2)
unnamed: R17.2, S5.4 (NO_2)
unnamed: C9.1, R37.1, S7.1 (COM_1)
unnamed: C11.1, R38.1, S10.1 (COM_1)
unnamed: R46.1, SOM1.JX2-95 (BANK13_LVDS_4_N)
unnamed: R45.1, SOM1.JX2-93 (BANK13_LVDS_4_P)
unnamed: R160.2, SOM1.JX2-96 (BANK13_LVDS_5_N)
unnamed: R39.2, SOM1.JX2-94 (BANK13_LVDS_5_P)
unnamed: C18.1, U21.43 (LDO)
unnamed: C16.1, U21.48 (Q1)
unnamed: C16.2, U21.47 (Q2)
unnamed: C17.1, U21.46 (Q3)
unnamed: C14.1, U21.13 (VREFOUT), U21.14 (VREFP)
unnamed: C15.1, U21.11 (VREF_BYP)
unnamed: R10.1, U21.42 (~RESET)

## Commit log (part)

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2025-03-14 3V3 Power subsystem modifications
2025-03-16 implementation of 1V8 and 2V5 systems
2025-03-16 minor label corrections
2025-04-01 PG_MODULE logic implemented
    Implementação da lógica do PowerGood.
    Faltando implementar um conector banana externo que pode substituir os provedores de referência para os I/O banks. Além dos LEDs indicadores de funcionamento.
2025-04-04 PG_CARRIER Implemented
2025-04-10 Schematic circuit implementations
2025-04-11 Circuit implementations
    decouplig caps for LDOs, TVS Diodes
2025-04-16 PWR_EN modifications
    Waiting for reset ic model
2025-04-18 PWR_EN reset ic implementation
2025-04-18 Early-Stage PCB layout modifications
2025-04-20 separated component groups for layout
2025-04-20 I/O Banks oltage selectors layout done
2025-04-21 Microzed PWR components placed
2025-04-21 Silk Screen Additions
    Voltage Selection table
    silkscreen improvements
2025-04-23 PWR Preliminary Routing
    Requires optimization
2025-05-05 RFB conector changed
2025-06-15 Major Power Schematic changes
    Changed Microzed carrier supply, removed VS connector and added 3V3 LDO instead
2025-06-15 Major changes to Schematic
2025-06-16 Power Schematic and Layout changes
    Não rodei DRC ainda
2025-06-17 Minor schematic changes
2025-06-21 UART-USB bridge removal
2025-06-21 Major rerouting and silk modifications
    Moved the power sensors below PC104 connector and brought external voltage connectors to the left side of the board.
2025-06-21 DRC and minor fixes
2025-06-29 Fix: Voltage translators OE to PG_VCCB instead of VCCIO
2025-08-21 fix: Fuducial improvements for PCBA
    Excluded extra fiducial marks, 3 left only
2025-08-26 add: Thermocouple connectors
2025-08-30 fix: DRC run
2025-09-04 add: Mounting Hole for interface board
2025-09-05 add: VCCB Voltage Selector
2025-09-07 add: GND Via Stiching
2025-09-07 fix: improved grounding
2026-05-14 Fix: switched voltage regulators connections
2026-05-17 feat: logic bridges removal from layout
2026-05-18 feat: DRC
2026-06-18 feat: PWR rerouting

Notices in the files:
README.md:
License: CERN-OHL-S-2.0
